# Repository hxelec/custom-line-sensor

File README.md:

# custom-line-sensor
A simple design for a custom line sensing array, using the well-known QRE1113GR reflective sensor, which is seen in most line followers (including crazy fast PID ones). The same design is also seen in the QTR series from Pololu.
Full tutorial is documented on my YouTube channel: https://www.youtube.com/watch?v=jIgIj2hZbxc
Notes: 
You really only need the QRE1113GR itself, and two resistors, however, I decided to add two decoupling capacitors for more stable signals. That makes the entire project just 18 parts, which is pretty simple.
Also, the tutorial PCB layout isn't the exact same as the one that I actually printed and used, for recording purposes. (It still works the exact same)
Nevertheless, the design files of the one I actually sent off to be manufactured are in this repository.

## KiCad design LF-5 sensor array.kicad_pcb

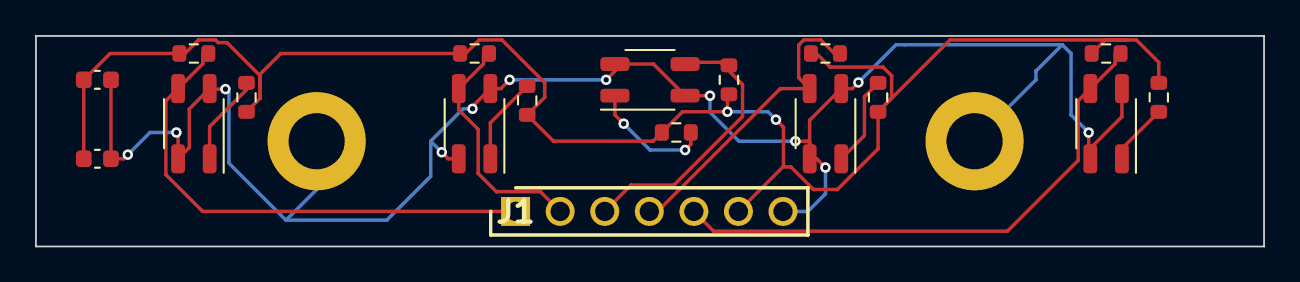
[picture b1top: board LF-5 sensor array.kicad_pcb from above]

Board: 2 copper layers, 70.0 x 12.0 mm, 20 parts (0 on the bottom side), 12 nets.

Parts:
C1: 0.1 uF; C_0603_1608Metric
C2: 1 uF; C_0603_1608Metric
H1, H2: M3 hole; MountingHole_3.2mm_M3_DIN965_Pad
J1: Pin Header 7P; HDRV7W64P0X254_1X7_1778X254X869P
R1, R3, R5, R7, R9: 220; R_0603_1608Metric
R2, R4, R6, R8, R10: 47k; R_0603_1608Metric
U1, U2, U3, U4, U5: QRE1113GR; OnSemi_CASE100CY

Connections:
/O1: J1.1, R2.2, U1.3
/O2: J1.2, R4.2, U2.3
/O3: J1.3, R6.2, U3.3
/O4: J1.4, R8.2, U4.3
/O5: J1.5, R10.2, U5.3
GND: C1.2, C2.2, H1.1, H2.1, J1.7, U1.2 (K), U1.4, U2.2 (K), U2.4, U3.2 (K), U3.4, U4.2 (K), U4.4, U5.2 (K), U5.4
unnamed: R1.2, U1.1 (A)
unnamed: R3.2, U2.1 (A)
unnamed: R5.2, U3.1 (A)
unnamed: R7.2, U4.1 (A)
unnamed: R9.2, U5.1 (A)
VCC: C1.1, C2.1, J1.6, R1.1, R2.1, R3.1, R4.1, R5.1, R6.1, R7.1, R8.1, R9.1, R10.1
